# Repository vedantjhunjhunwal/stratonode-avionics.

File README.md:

# StratoNode: avionics power & telemetry node for stratospheric UAVs

A flight-computer-class board for a fixed-wing UAV cruising at **50,000 ft (15.5 km), -70 °C,
15% sea-level air density**: input protection and hold-up, a 5 V / 3 A buck and 3V3 LDO,
firmware-controlled load shedding, two heater channels (battery box and avionics bay), an
STM32G474 (Cortex-M4F, CAN-FD), a barometer good to 10 mbar, and GNSS (GPS + NavIC), telemetry,
payload and CAN harness connectors.

The project covers the board end to end: power budget and failure analysis, schematic,
component selection, PCB placement, embedded C firmware, and a closed-loop flight simulation
that runs that firmware against battery, thermal and power models.

## What has been verified, and what has not

| | Status |
|---|---|
| Power, thermal, hold-up, solder-fatigue and vibration analysis | Done: `analysis/`, 12 pytest tests, report in `docs/ANALYSIS.md` |
| Schematic (KiCad 7) | Done: 104 parts, 66 nets. KiCad's exported netlist matches the design source pin for pin (314 pins); an ERC subset passes (KiCad 7's CLI has no ERC). |
| PCB | **Placed, not yet routed.** 80 x 56 mm, 4 layers (GND and 3V3 inner planes), all footprints placed with no courtyard overlaps. Routing is one Freerouting run (see below). |
| Firmware | Drivers, power manager, heaters, NMEA, CAN-FD telemetry: 136 unit checks under AddressSanitizer/UBSan. Cross-compiles for the STM32G474 with no heap. **Not run on hardware**: I2C/SPI/UART/FDCAN peripheral drivers on the target are stubs until the board exists. |
| Flight simulation | 10.5 h mission, 5 seeds, firmware in the loop, with and without load shedding |
| Fabricated, built, flown | **No.** |

## Key results

**Power and thermal** (`docs/ANALYSIS.md`)
- Mission energy **135.8 Wh** (analysis) vs **136.5 Wh** (closed-loop simulation, mean of 5 seeds). Pack: **4S5P** 18650, 8% margin at end of life and +5 °C, with 20% reserve.
- Peak 5 V rail 1.91 A against the 3 A buck (36% margin). Junction temperatures checked at -70 °C cruise and +50 °C hot ground; all parts inside their ratings.
- Unheated, the avionics bay would settle at **-57.5 °C**, below the -40 °C rating of most parts. A 2 W bay heater holds -25 °C. The battery heater (12.6 W) warms a cold-soaked pack from -30 °C to +5 °C in 54 min.

**Design against failure**
- **Hold-up:** a 50 ms connector dropout under vibration needs **24,251 µF** if every load stays on, but only **999 µF** if firmware sheds the radio, payload *and both heaters* within 0.35 ms (INA226 ALERT → EXTI interrupt). Fitted: 3 × 470 µF polymer (1340 µF at -55 °C). The bulk caps are polymer, not electrolytic, because at -55 °C the electrolytics' ESR would add a 0.7 V step.
- **Simulation, 5 seeds, 153 dropouts of 2-50 ms:** **0 brownout resets** with load shedding vs **111** without.
- **Solder fatigue (Engelmaier, 1000-flight target at 0.1% failures):** 2512 shunts fail even in the heated bay, so the board uses 1206; the bay heater is what keeps 1206/1210 parts above target.
- **Vibration (Steinberg):** board fundamental 650 Hz, worst component deflection margin 6.2×.
- **Sensor faults:** a 20-minute battery-NTC open circuit is detected and ridden out on open-loop heater duty; 98 injected I2C bus lock-ups were all recovered by clocking out the stuck slave.
- **Data integrity:** all 3,795 injected CAN-FD bit errors caught (CRC-8 + alive counter). NMEA's XOR checksum let corrupted GNSS fixes through; a two-fix confirmation gate now holds the residual error to ≤100 m (11 of 36,403 corrupted sentences), where corrupted fixes previously got through with up to 15.5 km altitude error.

## Layout

```
analysis/   Python: ISA atmosphere, power budget, battery sizing, thermal, brown-out, hold-up,
            Engelmaier solder fatigue, Steinberg vibration. design.py holds every input.
hw/         parts.py (design source) -> gen_schematic.py -> KiCad schematic
            check_schematic.py (netlist round trip + ERC subset), gen_pcb.py (placement, planes,
            routing hand-off, DRC, Gerbers), make_bom.py
fw/         include/, src/   drivers (INA226, TMP117, MS5611, I2C recovery), power manager,
                             heater PI, NMEA (GPS+NavIC), CAN-FD telemetry, app layer
            tests/           unit tests with register-level fake devices
            sim/             closed-loop flight simulation
            target/          STM32G474 startup, linker script, register-level main, build script
results/    analysis.json, sim/*.json|csv, flight_sim.png, pcb_placement.png, schematic PDF
```

## Build and run

```bash
# analysis
(cd analysis && python3 -m pytest -q tests && python3 -m stratonode_analysis.report)
# firmware: unit tests, simulation campaign, STM32G474 cross-compile (gcc-arm-none-eabi, libnewlib-arm-none-eabi)
(cd fw && make test && make sim && make m4)
python3 tools/plot_sim.py
# hardware (KiCad 7 with its Python module)
cd hw && python3 gen_schematic.py && python3 check_schematic.py && python3 make_bom.py
python3 gen_pcb.py place && python3 gen_pcb.py route
java -jar freerouting-1.9.0.jar -de stratonode/stratonode.dsn -do stratonode/stratonode.ses -mp 40
python3 gen_pcb.py import      # routes in, outer GND pours, DRC report, Gerbers/drill/pos in stratonode/fab/
```

## Design notes

- **Why the ideal diode (LM74700 + N-FET):** reverse-polarity protection without a diode drop, and it
  stops the hold-up caps back-feeding a dropped input. VIN is sensed *before* it, so VIN collapses
  within microseconds of a connector opening while VBAT is still held up. That gap is how firmware
  sees a dropout in time to shed load.
- **Two I2C buses:** the external GNSS/compass harness is on I2C2, so a damaged cable cannot hang the
  INA226/TMP117 bus that the power and heater loops depend on.
- **Crystal, not RC:** CAN-FD bit timing needs better than 0.5% clock error at -40 °C.
- **Tag-Connect for SWD:** no debug header on board to vibrate loose in flight.
- **Pixhawk-standard JST-GH pinouts** for CAN, GNSS and telemetry, with positive latches.

## Limitations (read before quoting numbers)

- **Nothing here has been built or flown.** Thermal and electrical models use datasheet and typical
  values; anything marked ASSUMED in `analysis/stratonode_analysis/design.py` needs measuring.
- **The PCB is placed but not routed**, and DRC has not been run on a routed board. Before ordering:
  route, run DRC, and review the buck layout loop by hand. Check the TPS62933 RT/SS values and the
  MCU alternate-function pin map against the datasheets in STM32CubeMX.
- **Engelmaier and Steinberg are screening models.** Engelmaier is good to about a factor of 2; the
  vibration PSD is an assumed envelope, not a measured flight spectrum.
- **The simulation is not hardware-in-the-loop.** It checks that the logic is right, not its timing on the MCU.
- The thermal model treats each enclosure as a single lumped node, and cold-day ISA as the ambient.

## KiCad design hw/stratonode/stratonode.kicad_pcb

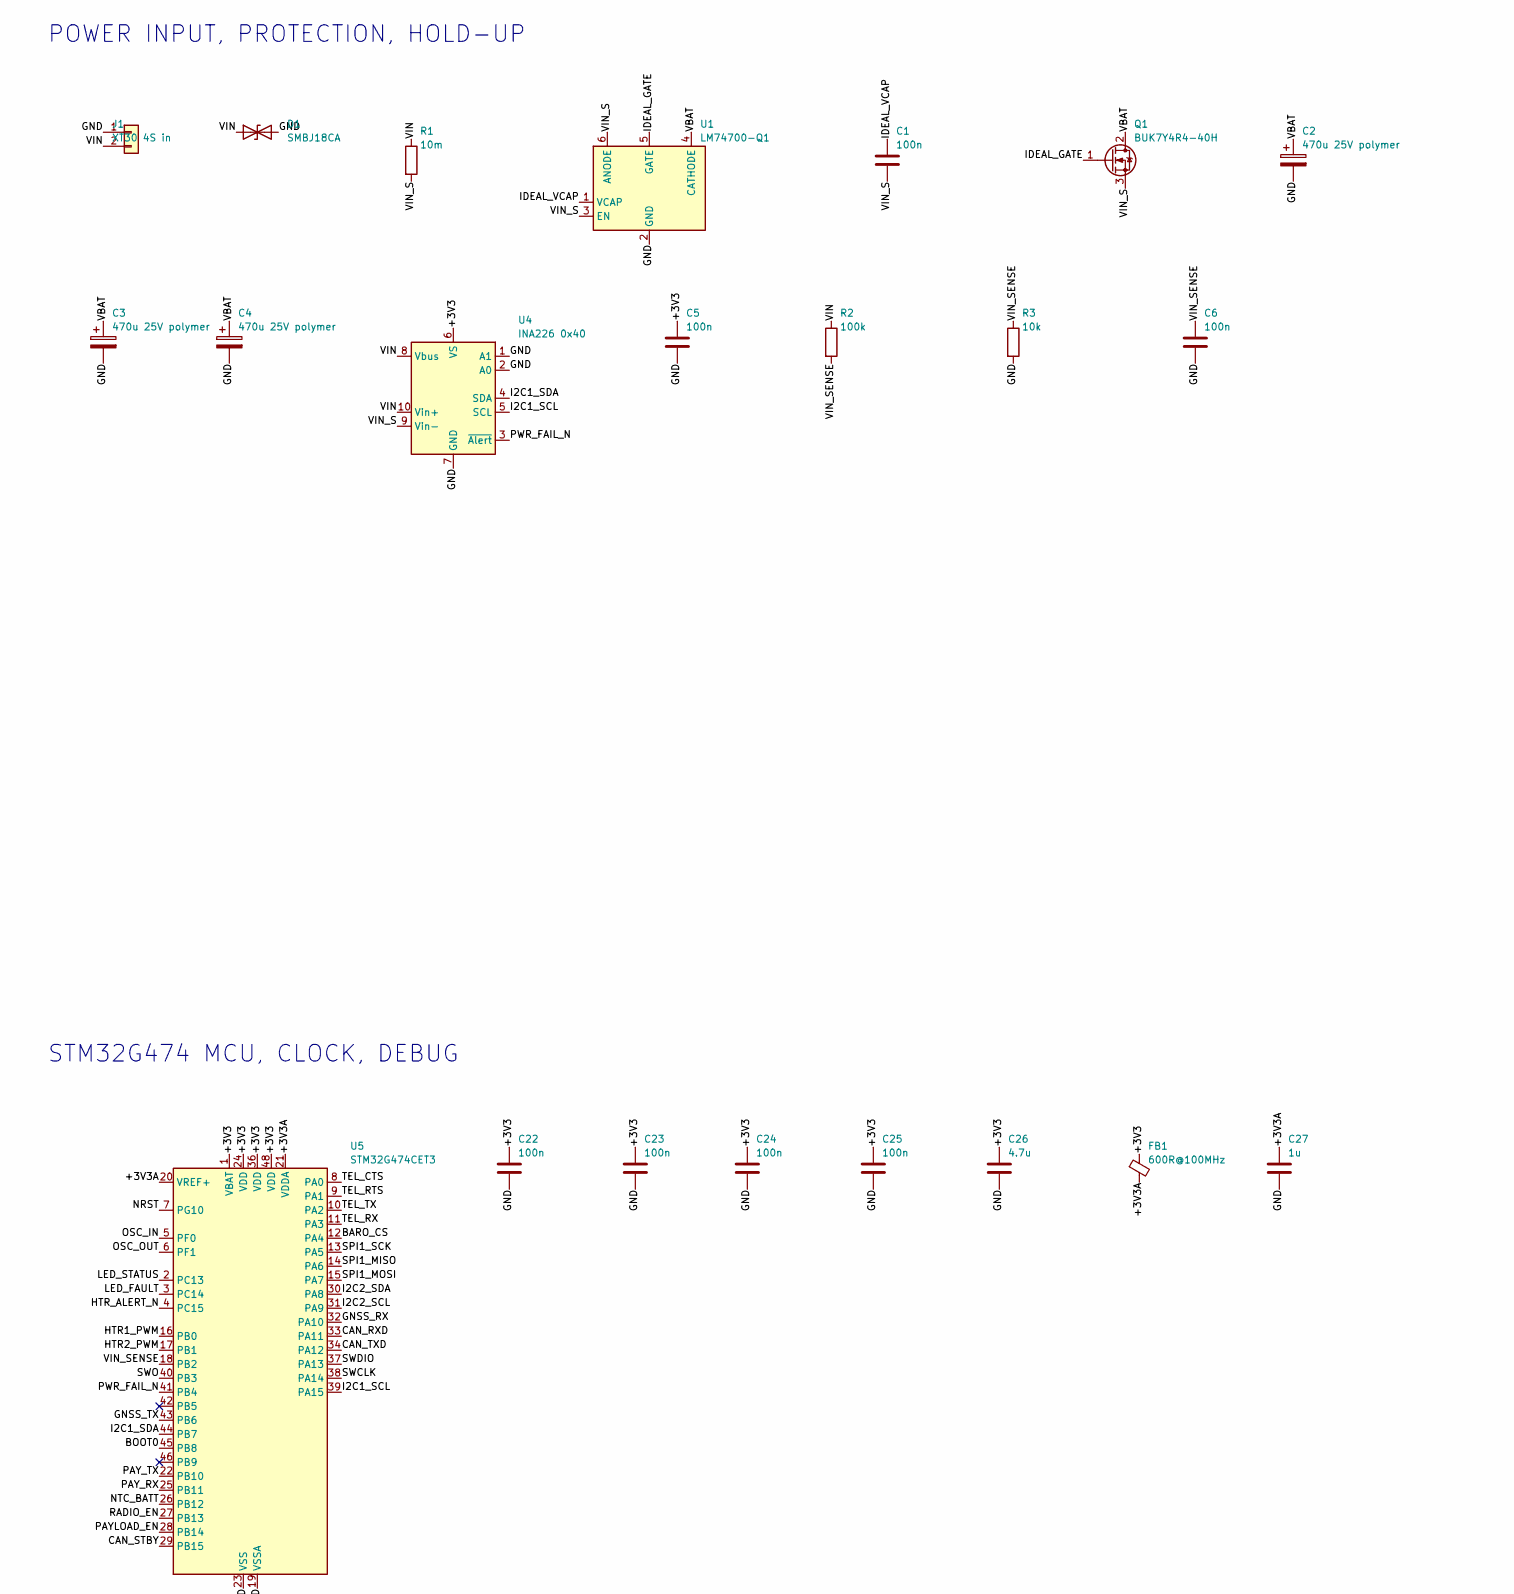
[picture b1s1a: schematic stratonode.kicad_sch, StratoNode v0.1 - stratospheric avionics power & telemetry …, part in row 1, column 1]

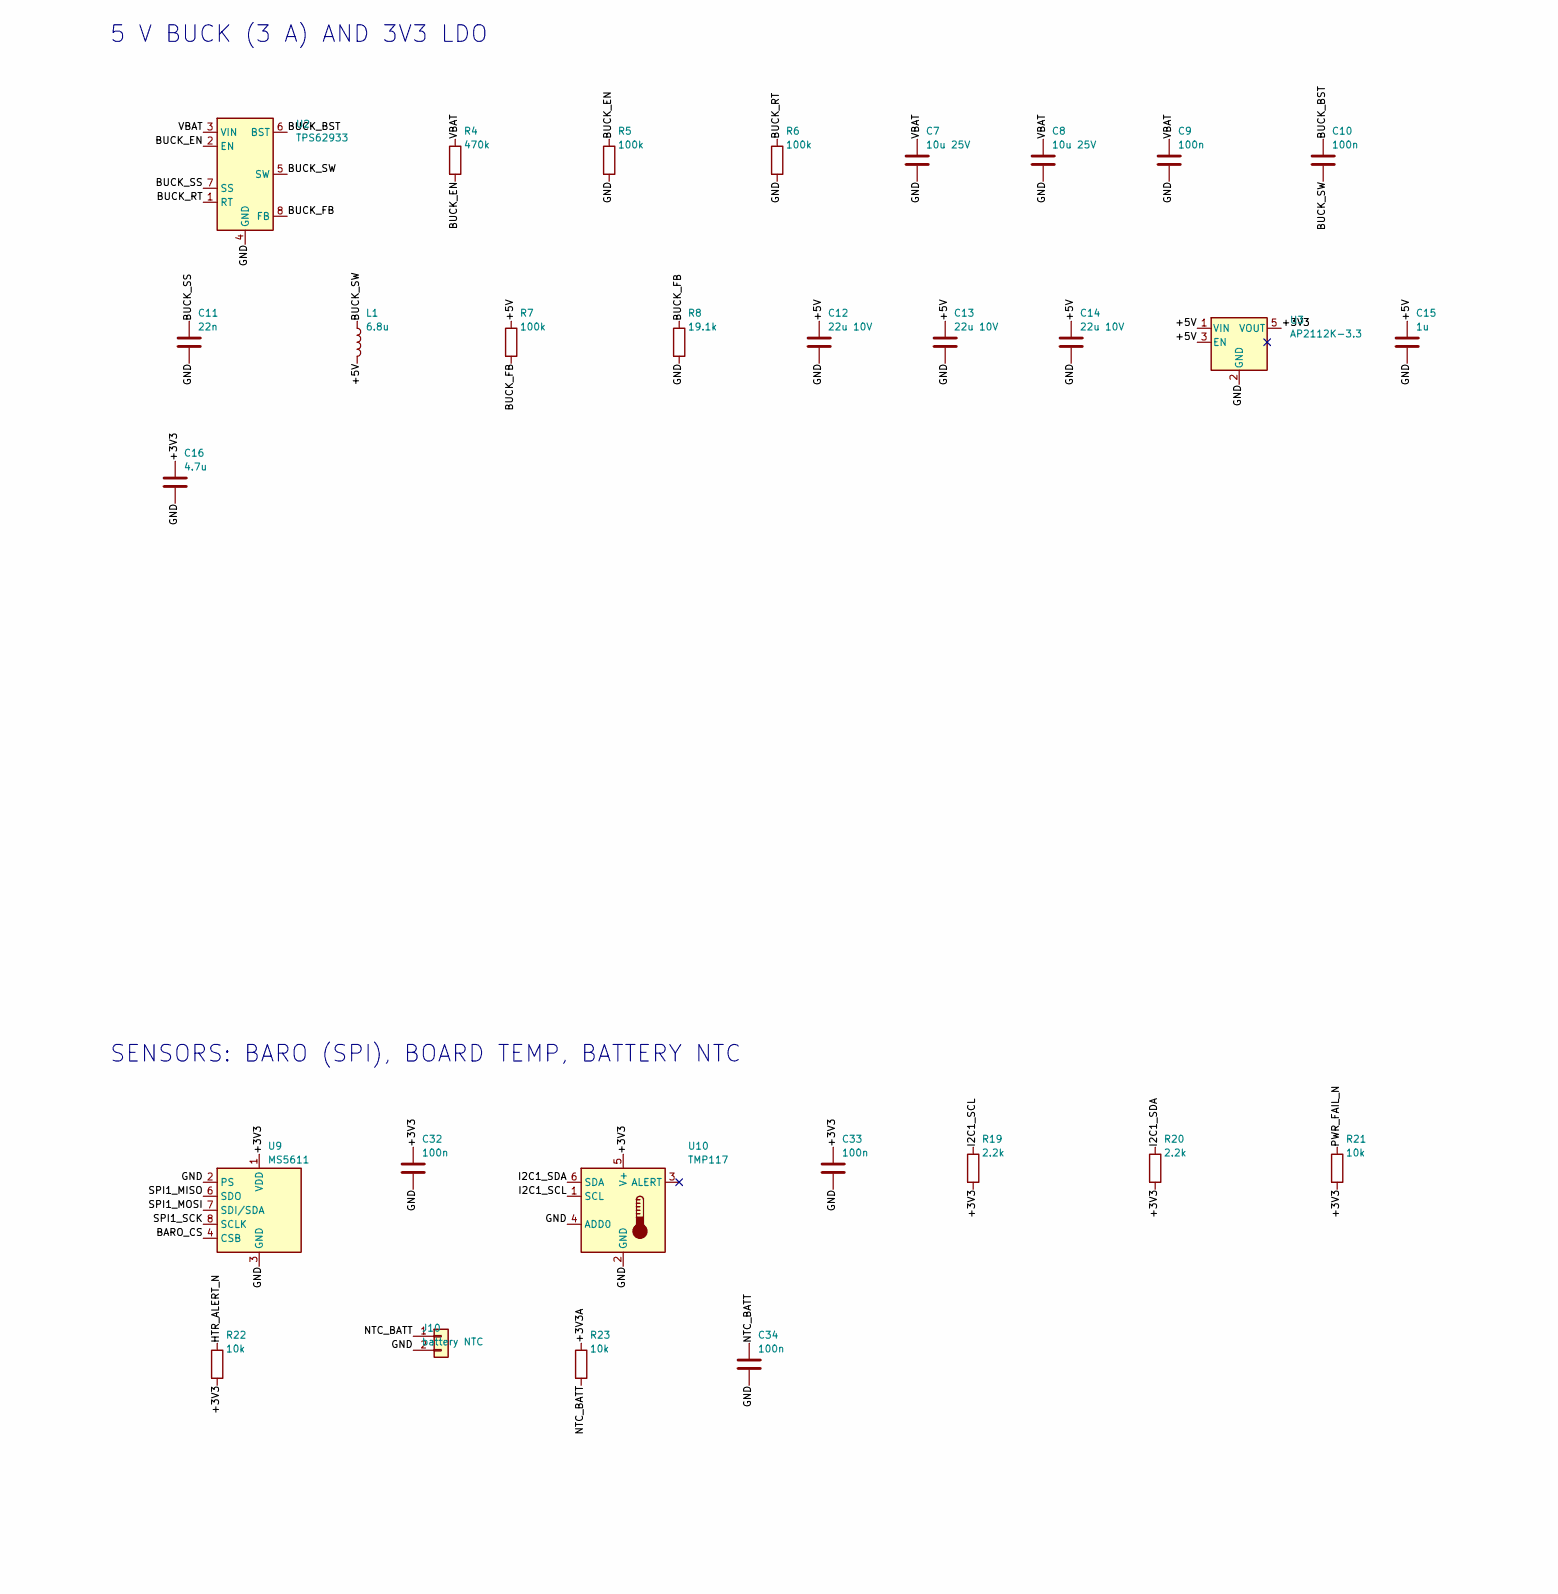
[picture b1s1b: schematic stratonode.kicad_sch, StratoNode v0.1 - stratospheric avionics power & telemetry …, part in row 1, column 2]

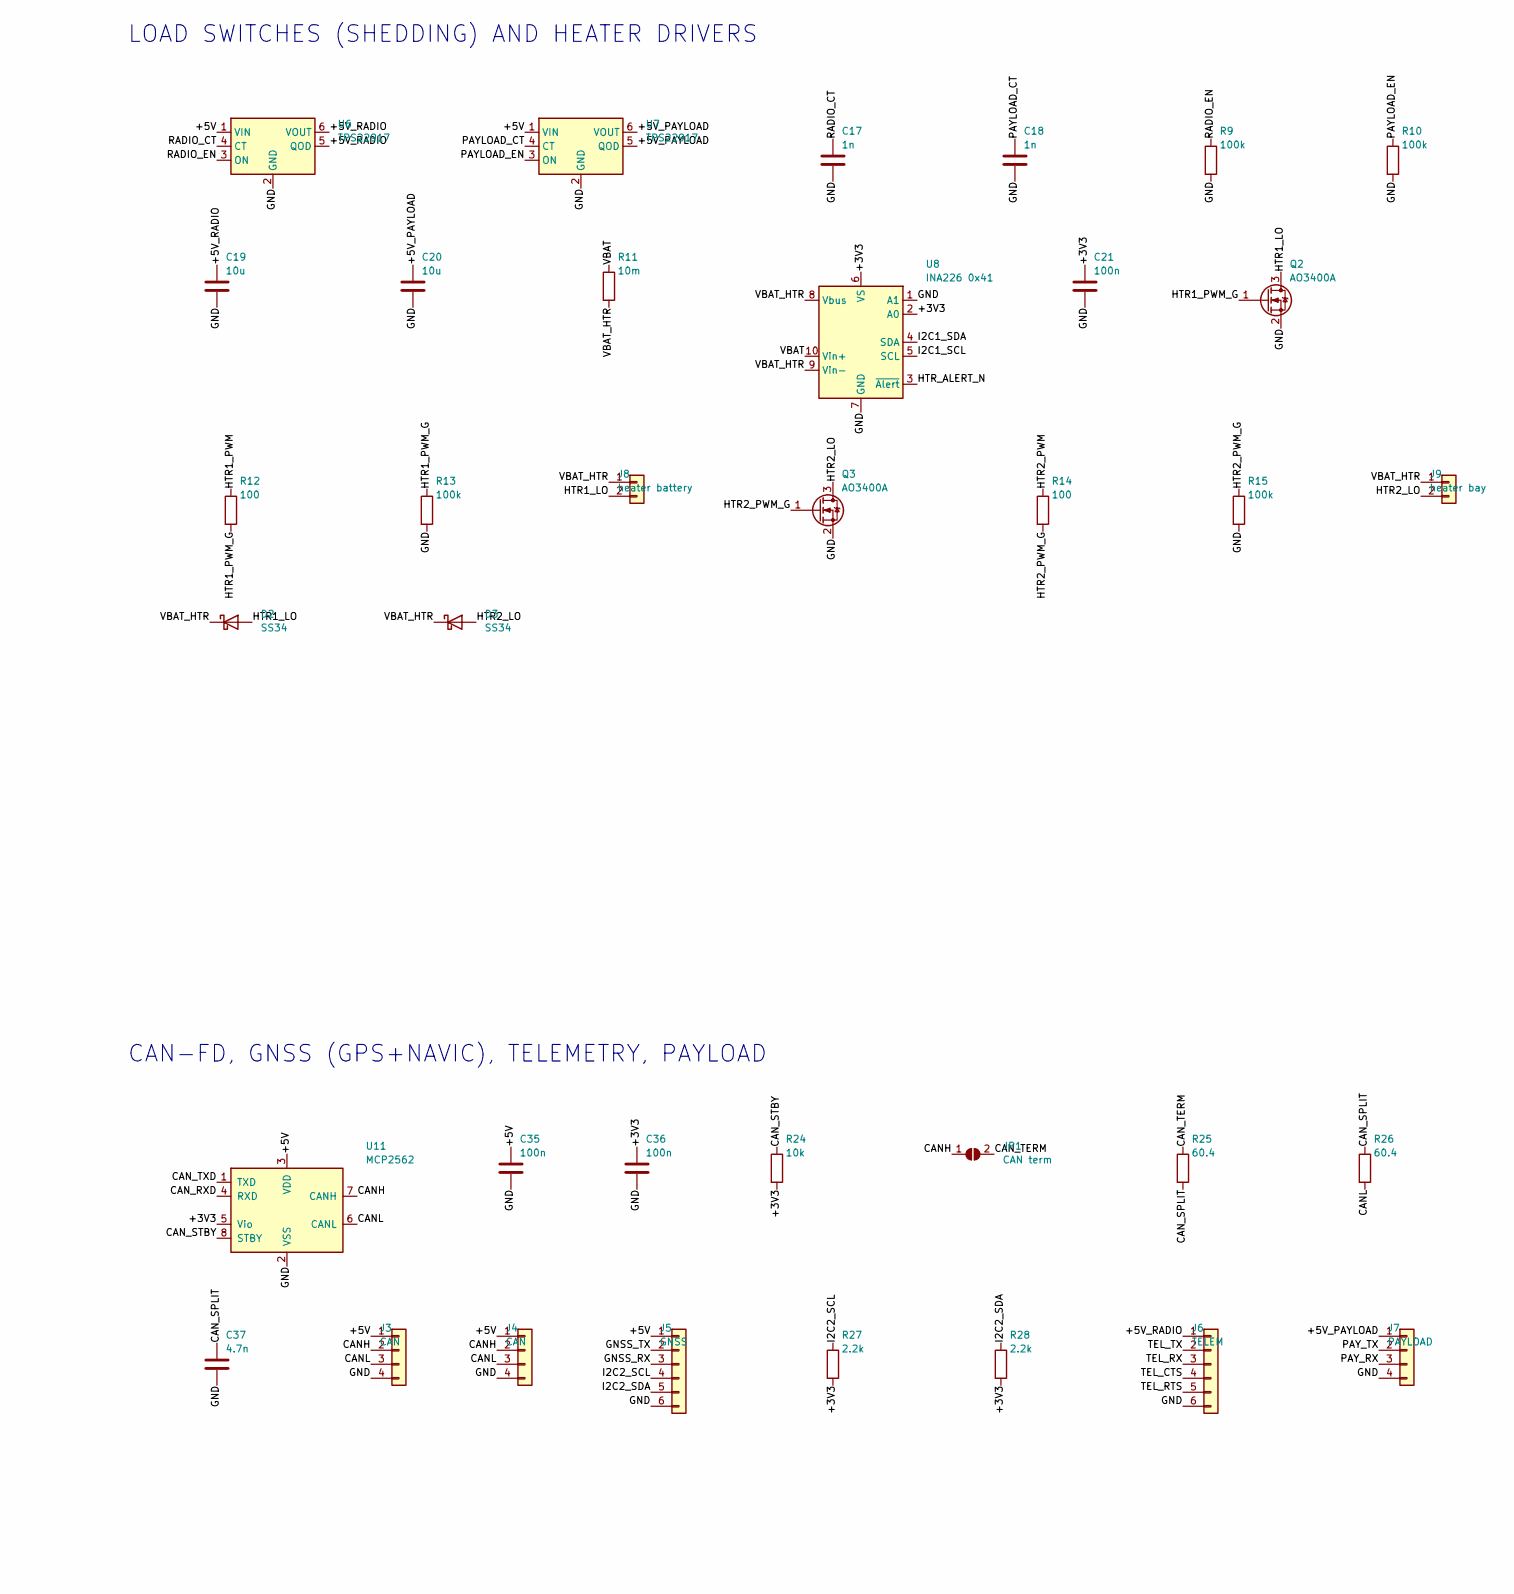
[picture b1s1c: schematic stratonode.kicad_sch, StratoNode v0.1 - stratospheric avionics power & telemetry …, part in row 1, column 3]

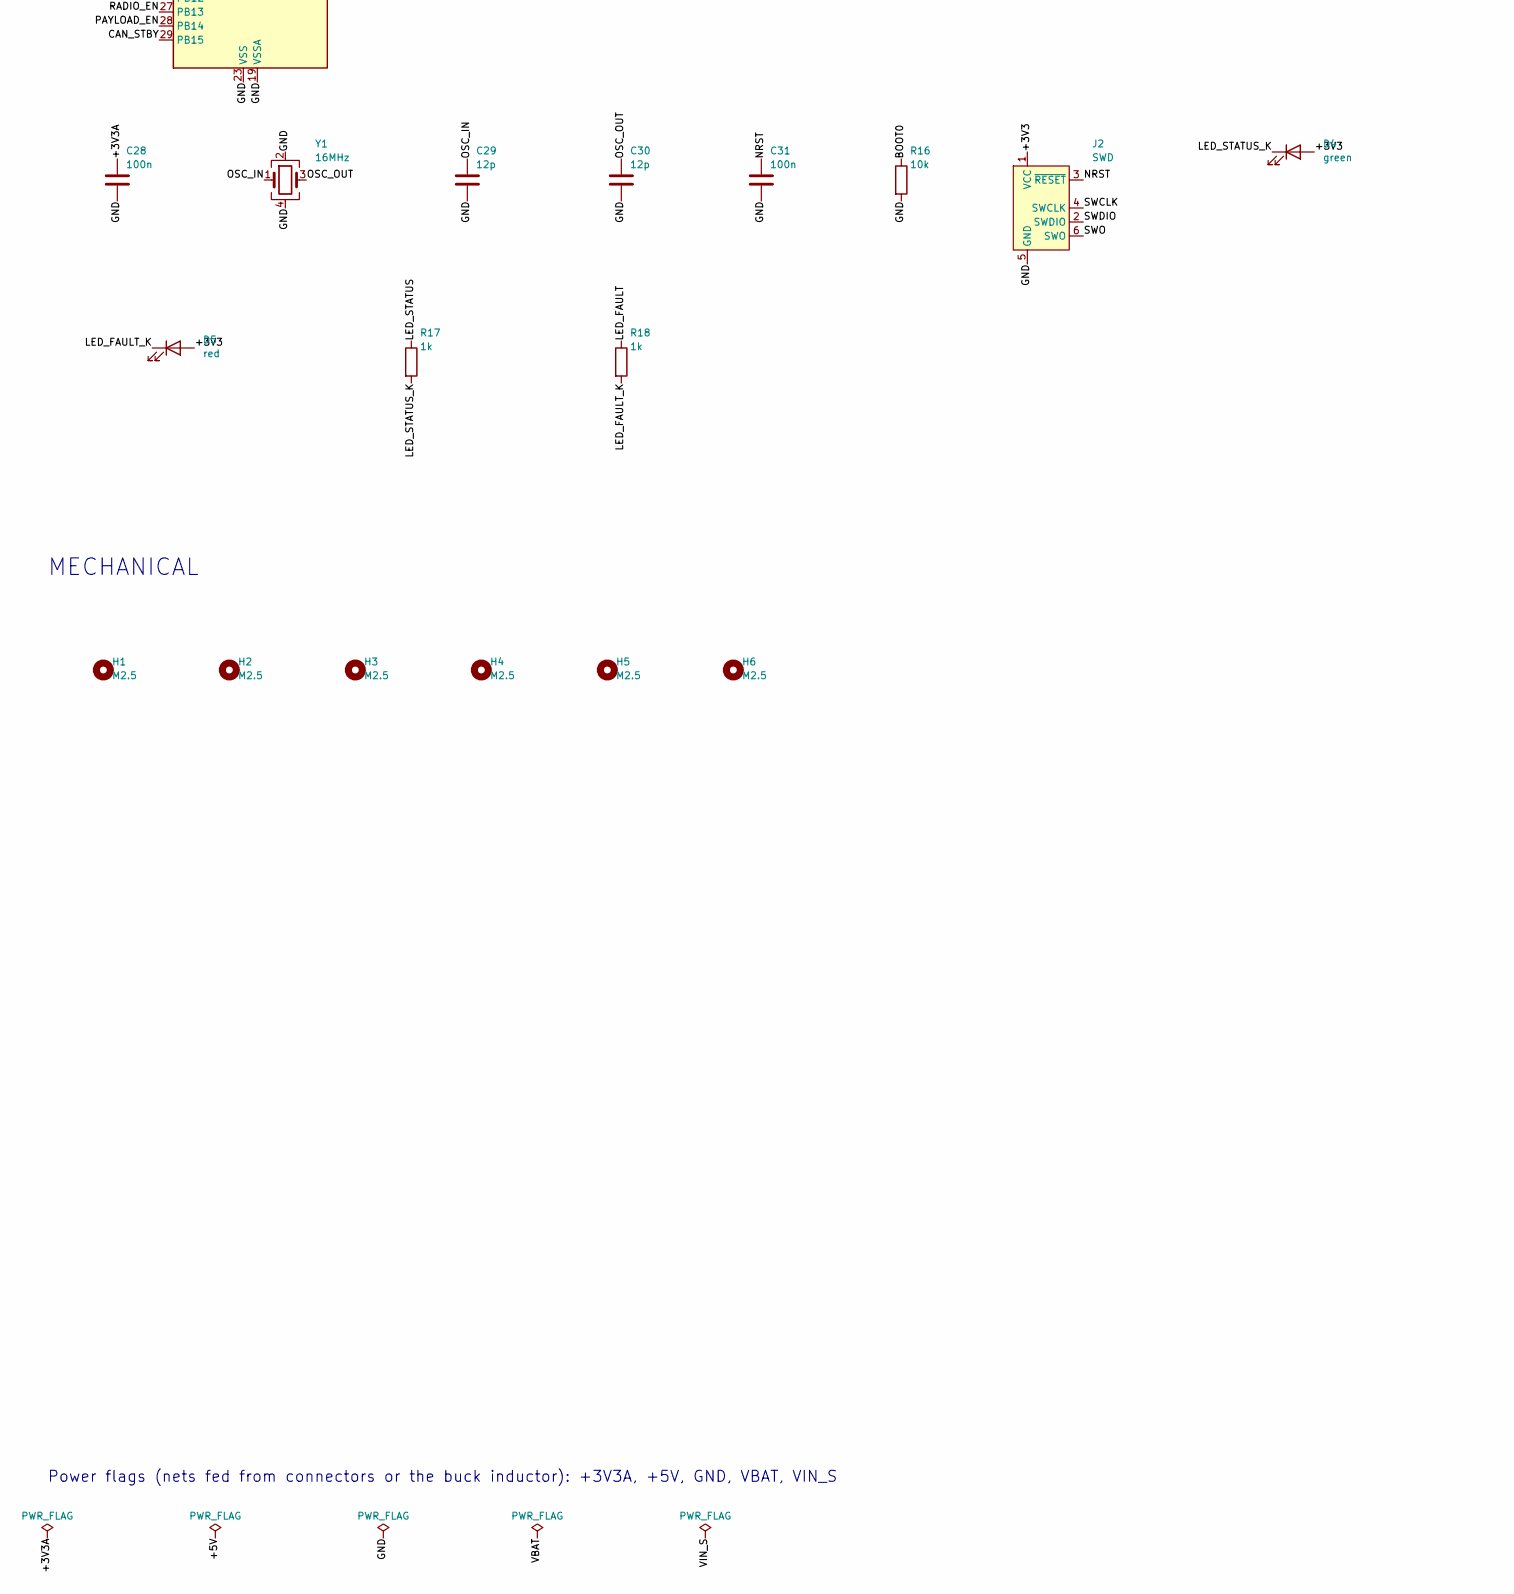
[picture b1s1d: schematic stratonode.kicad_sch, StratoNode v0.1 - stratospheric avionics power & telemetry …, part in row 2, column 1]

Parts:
C1, C5, C6, C9, C10, C21, C22, C23, C24, C25, C28, C31, C32, C33, C34, C35, C36: 100n; C_0603_1608Metric; MPN 100n X7R, -55..125 C
C2, C3, C4: 470u 25V polymer; CP_Elec_8x10; MPN 25 V 470 uF aluminium polymer, -55..105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
C7, C8: 10u 25V; C_0805_2012Metric; MPN 10u 25V X7R, -55..125 C
C11: 22n; C_0603_1608Metric; MPN 22n X7R, -55..125 C
C12, C13, C14: 22u 10V; C_0805_2012Metric; MPN 22u 10V X7R, -55..125 C
C15, C27: 1u; C_0603_1608Metric; MPN 1u X7R, -55..125 C
C16, C26: 4.7u; C_0805_2012Metric; MPN 4.7u X7R, -55..125 C
C17, C18: 1n; C_0603_1608Metric; MPN 1n X7R, -55..125 C
C19, C20: 10u; C_0805_2012Metric; MPN 10u X7R, -55..125 C
C29, C30: 12p; C_0603_1608Metric; MPN 12 pF C0G
C37: 4.7n; C_0603_1608Metric; MPN 4.7n X7R, -55..125 C
D1: SMBJ18CA; D_SMB; MPN SMBJ18CA
D2, D3: SS34; D_SMA; MPN SS34
D4: green; LED_0603_1608Metric; MPN green 0603 LED
D5: red; LED_0603_1608Metric; MPN red 0603 LED
FB1: 600R@100MHz; L_0603_1608Metric; MPN BLM18KG601SN1D
H1, H2, H3, H4, H5, H6: M2.5; MountingHole_2.7mm_M2.5; MPN M2.5 standoff
J1: XT30 4S in; AMASS_XT30PW-M_1x02_P2.50mm_Horizontal; MPN AMASS XT30PW-M
J2: SWD; Tag-Connect_TC2030-IDC-NL_2x03_P1.27mm_Vertical; MPN Tag-Connect TC2030-NL
J3, J4: CAN; JST_GH_SM04B-GHS-TB_1x04-1MP_P1.25mm_Horizontal; MPN JST SM04B-GHS-TB
J5: GNSS; JST_GH_SM06B-GHS-TB_1x06-1MP_P1.25mm_Horizontal; MPN JST SM06B-GHS-TB
J6: TELEM; JST_GH_SM06B-GHS-TB_1x06-1MP_P1.25mm_Horizontal; MPN JST SM06B-GHS-TB
J7: PAYLOAD; JST_GH_SM04B-GHS-TB_1x04-1MP_P1.25mm_Horizontal; MPN JST SM04B-GHS-TB
J8: heater battery; JST_XH_B2B-XH-A_1x02_P2.50mm_Vertical; MPN JST B2B-XH-A
J9: heater bay; JST_XH_B2B-XH-A_1x02_P2.50mm_Vertical; MPN JST B2B-XH-A
J10: battery NTC; JST_GH_SM02B-GHS-TB_1x02-1MP_P1.25mm_Horizontal; MPN JST SM02B-GHS-TB
JP1: CAN term; SolderJumper-2_P1.3mm_Open_RoundedPad1.0x1.5mm
L1: 6.8u; L_Bourns_SRP7028A_7.3x6.6mm; MPN Bourns SRP7028A-6R8M
Q1: BUK7Y4R4-40H; TO-252-2; MPN 40 V, 4.4 mOhm N-FET (ideal diode)
Q2, Q3: AO3400A; SOT-23; MPN AO3400A
R1, R11: 10m; R_1206_3216Metric; MPN 10 mOhm 1206 0.5 W current shunt
R2, R5, R6, R7, R9, R10, R13, R15: 100k; R_0603_1608Metric; MPN 100k 1% 0603, AEC-Q200, -55..155 C
R3, R16, R21, R22, R23, R24: 10k; R_0603_1608Metric; MPN 10k 1% 0603, AEC-Q200, -55..155 C
R4: 470k; R_0603_1608Metric; MPN 470k 1% 0603, AEC-Q200, -55..155 C
R8: 19.1k; R_0603_1608Metric; MPN 19.1k 1% 0603, AEC-Q200, -55..155 C
R12, R14: 100; R_0603_1608Metric; MPN 100 1% 0603, AEC-Q200, -55..155 C
R17, R18: 1k; R_0603_1608Metric; MPN 1k 1% 0603, AEC-Q200, -55..155 C
R19, R20, R27, R28: 2.2k; R_0603_1608Metric; MPN 2.2k 1% 0603, AEC-Q200, -55..155 C
R25, R26: 60.4; R_0603_1608Metric; MPN 60.4 1% 0603, AEC-Q200, -55..155 C
U1: LM74700-Q1; SOT-23-6; MPN LM74700QDBVRQ1
U2: TPS62933; SOT-583-8; MPN TPS62933DRLR
U3: AP2112K-3.3; SOT-23-5; MPN AP2112K-3.3TRG1
U4: INA226 0x40; VSSOP-10_3x3mm_P0.5mm; MPN INA226AIDGSR
U5: STM32G474CET3; LQFP-48_7x7mm_P0.5mm; MPN STM32G474CET3
U6, U7: TPS22917; SOT-23-6; MPN TPS22917DBVR
U8: INA226 0x41; VSSOP-10_3x3mm_P0.5mm; MPN INA226AIDGSR
U9: MS5611; LGA-8_3x5mm_P1.25mm; MPN MS561101BA03-50
U10: TMP117; WSON-6-1EP_2x2mm_P0.65mm_EP1x1.6mm; MPN TMP117MAIDRVR
U11: MCP2562; SOIC-8_3.9x4.9mm_P1.27mm; MPN MCP2562FD-E/SN
Y1: 16MHz; Crystal_SMD_3225-4Pin_3.2x2.5mm; MPN 16 MHz 10 pF, -40..125 C

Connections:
+3V3: C5.1, C16.1, C21.1, C22.1, C23.1, C24.1, C25.1, C26.1, C32.1, C33.1, C36.1, D4.2 (A), D5.2 (A), FB1.1, J2.1 (VCC), R19.2, R20.2, R21.2, R22.2, R24.2, R27.2, R28.2, U3.5 (VOUT), U4.6 (VS), U5.1 (VBAT), U5.24 (VDD), U5.36 (VDD), U5.48 (VDD), U8.2 (A0), U8.6 (VS), U9.1 (VDD), U10.5 (V+), U11.5 (Vio)
+3V3A: C27.1, C28.1, FB1.2, R23.1, U5.20 (VREF+), U5.21 (VDDA)
+5V: C12.1, C13.1, C14.1, C15.1, C35.1, J3.1, J4.1, J5.1, L1.2, R7.1, U3.1 (VIN), U3.3 (EN), U6.1 (VIN), U7.1 (VIN), U11.3 (VDD)
+5V_PAYLOAD: C20.1, J7.1, U7.5 (QOD), U7.6 (VOUT)
+5V_RADIO: C19.1, J6.1, U6.5 (QOD), U6.6 (VOUT)
BARO_CS: U5.12 (PA4), U9.4 (CSB), U9.5 (CSB)
BOOT0: R16.1, U5.45 (PB8)
BUCK_BST: C10.1, U2.6 (BST)
BUCK_EN: R4.2, R5.1, U2.2 (EN)
BUCK_FB: R7.2, R8.1, U2.8 (FB)
BUCK_RT: R6.1, U2.1 (RT)
BUCK_SS: C11.1, U2.7 (SS)
BUCK_SW: C10.2, L1.1, U2.5 (SW)
CANH: J3.2, J4.2, JP1.1 (A), U11.7 (CANH)
CANL: J3.3, J4.3, R26.2, U11.6 (CANL)
CAN_RXD: U5.33 (PA11), U11.4 (RXD)
CAN_SPLIT: C37.1, R25.2, R26.1
CAN_STBY: R24.1, U5.29 (PB15), U11.8 (STBY)
CAN_TERM: JP1.2 (B), R25.1
CAN_TXD: U5.34 (PA12), U11.1 (TXD)
GND: C2.2, C3.2, C4.2, C5.2, C6.2, C7.2, C8.2, C9.2, C11.2, C12.2, C13.2, C14.2, C15.2, C16.2, C17.2, C18.2, C19.2, C20.2, C21.2, C22.2, C23.2, C24.2, C25.2, C26.2, C27.2, C28.2, C29.2, C30.2, C31.2, C32.2, C33.2, C34.2, C35.2, C36.2, C37.2, D1.2 (A2), J1.1, J2.5 (GND), J3.4, J4.4, J5.6, J6.6, J7.4, J10.2, Q2.2 (S), Q3.2 (S), R3.2, R5.2, R6.2, R8.2, R9.2, R10.2, R13.2, R15.2, R16.2, U1.2 (GND), U2.4 (GND), U3.2 (GND), U4.1 (A1), U4.2 (A0), U4.7 (GND), U5.19 (VSSA), U5.23 (VSS), U5.35 (VSS), U5.47 (VSS), U6.2 (GND), U7.2 (GND), U8.1 (A1), U8.7 (GND), U9.2 (PS), U9.3 (GND), U10.2 (GND), U10.4 (ADD0), U11.2 (VSS), Y1.2, Y1.4
GNSS_RX: J5.3, U5.32 (PA10)
GNSS_TX: J5.2, U5.43 (PB6)
HTR1_LO: D2.2 (A), J8.2, Q2.3 (D)
HTR1_PWM: R12.1, U5.16 (PB0)
HTR1_PWM_G: Q2.1 (G), R12.2, R13.1
HTR2_LO: D3.2 (A), J9.2, Q3.3 (D)
HTR2_PWM: R14.1, U5.17 (PB1)
HTR2_PWM_G: Q3.1 (G), R14.2, R15.1
HTR_ALERT_N: R22.1, U5.4 (PC15), U8.3 (~Alert)
I2C1_SCL: R19.1, U4.5 (SCL), U5.39 (PA15), U8.5 (SCL), U10.1 (SCL)
I2C1_SDA: R20.1, U4.4 (SDA), U5.44 (PB7), U8.4 (SDA), U10.6 (SDA)
I2C2_SCL: J5.4, R27.1, U5.31 (PA9)
I2C2_SDA: J5.5, R28.1, U5.30 (PA8)
IDEAL_GATE: Q1.1 (G), U1.5 (GATE)
IDEAL_VCAP: C1.1, U1.1 (VCAP)
LED_FAULT: R18.1, U5.3 (PC14)
LED_FAULT_K: D5.1 (K), R18.2
LED_STATUS: R17.1, U5.2 (PC13)
LED_STATUS_K: D4.1 (K), R17.2
NRST: C31.1, J2.3 (~RESET), U5.7 (PG10)
NTC_BATT: C34.1, J10.1, R23.2, U5.26 (PB12)
OSC_IN: C29.1, U5.5 (PF0), Y1.1
OSC_OUT: C30.1, U5.6 (PF1), Y1.3
PAYLOAD_CT: C18.1, U7.4 (CT)
PAYLOAD_EN: R10.1, U5.28 (PB14), U7.3 (ON)
PAY_RX: J7.3, U5.25 (PB11)
PAY_TX: J7.2, U5.22 (PB10)
PWR_FAIL_N: R21.1, U4.3 (~Alert), U5.41 (PB4)
RADIO_CT: C17.1, U6.4 (CT)
RADIO_EN: R9.1, U5.27 (PB13), U6.3 (ON)
SPI1_MISO: U5.14 (PA6), U9.6 (SDO)
SPI1_MOSI: U5.15 (PA7), U9.7 (SDI/SDA)
SPI1_SCK: U5.13 (PA5), U9.8 (SCLK)
SWCLK: J2.4 (SWCLK), U5.38 (PA14)
SWDIO: J2.2 (SWDIO), U5.37 (PA13)
SWO: J2.6 (SWO), U5.40 (PB3)
TEL_CTS: J6.4, U5.8 (PA0)
TEL_RTS: J6.5, U5.9 (PA1)
TEL_RX: J6.3, U5.11 (PA3)
TEL_TX: J6.2, U5.10 (PA2)
VBAT: C2.1, C3.1, C4.1, C7.1, C8.1, C9.1, Q1.2 (D), R4.1, R11.1, U1.4 (CATHODE), U2.3 (VIN), U8.10 (Vin+)
VBAT_HTR: D2.1 (K), D3.1 (K), J8.1, J9.1, R11.2, U8.8 (Vbus), U8.9 (Vin-)
VIN: D1.1 (A1), J1.2, R1.1, R2.1, U4.8 (Vbus), U4.10 (Vin+)
VIN_S: C1.2, Q1.3 (S), R1.2, U1.3 (EN), U1.6 (ANODE), U4.9 (Vin-)
VIN_SENSE: C6.1, R2.2, R3.1, U5.18 (PB2)

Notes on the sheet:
POWER INPUT, PROTECTION, HOLD-UP
5 V BUCK (3 A) AND 3V3 LDO
LOAD SWITCHES (SHEDDING) AND HEATER DRIVERS
STM32G474 MCU, CLOCK, DEBUG
SENSORS: BARO (SPI), BOARD TEMP, BATTERY NTC
CAN-FD, GNSS (GPS+NAVIC), TELEMETRY, PAYLOAD
MECHANICAL
Power flags (nets fed from connectors or the buck inductor): +3V3A, +5V, GND, VBAT, VIN_S

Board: 4 copper layers, 104 parts (0 on the bottom side), 66 nets, no tracks yet.

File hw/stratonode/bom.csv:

Qty,References,Value,Part / rating,Footprint,Why this part
17,C1 C5 C6 C9 C10 C21 C22 C23 C24 C25 C28 C31 C32 C33 C34 C35 C36,100n,"100n X7R, -55..125 C",C_0603_1608Metric,ADC analog-watchdog input: fast dropout detection
1,C11,22n,"22n X7R, -55..125 C",C_0603_1608Metric,
3,C12 C13 C14,22u 10V,"22u 10V X7R, -55..125 C",C_0805_2012Metric,
2,C15 C27,1u,"1u X7R, -55..125 C",C_0603_1608Metric,
2,C16 C26,4.7u,"4.7u X7R, -55..125 C",C_0805_2012Metric,
2,C17 C18,1n,"1n X7R, -55..125 C",C_0603_1608Metric,slew rate: limits inrush from radio input caps
2,C19 C20,10u,"10u X7R, -55..125 C",C_0805_2012Metric,
3,C2 C3 C4,470u 25V polymer,"25 V 470 uF aluminium polymer, -55..105 C",CP_Elec_8x10,hold-up: 3 x 470 uF rides a 50 ms dropout with load shedding
2,C29 C30,12p,12 pF C0G,C_0603_1608Metric,
1,C37,4.7n,"4.7n X7R, -55..125 C",C_0603_1608Metric,
2,C7 C8,10u 25V,"10u 25V X7R, -55..125 C",C_0805_2012Metric,
1,D1,SMBJ18CA,SMBJ18CA,D_SMB,bidirectional TVS: clamps load dump below the buck's 30 V rating; blocks nothing
2,D2 D3,SS34,SS34,D_SMA,clamps harness-inductance kickback at heater switch-off
1,D4,green,green 0603 LED,LED_0603_1608Metric,
1,D5,red,red 0603 LED,LED_0603_1608Metric,
1,FB1,600R@100MHz,BLM18KG601SN1D,L_0603_1608Metric,isolates the ADC reference from digital noise
6,H1 H2 H3 H4 H5 H6,M2.5,M2.5 standoff,MountingHole_2.7mm_M2.5,
1,J1,XT30 4S in,AMASS XT30PW-M,AMASS_XT30PW-M_1x02_P2.50mm_Horizontal,locking-friction power connector; 4S pack 12.0-16.8 V
1,J10,battery NTC,JST SM02B-GHS-TB,JST_GH_SM02B-GHS-TB_1x02-1MP_P1.25mm_Horizontal,10k NTC on the cells
1,J2,SWD,Tag-Connect TC2030-NL,Tag-Connect_TC2030-IDC-NL_2x03_P1.27mm_Vertical,no connector fitted: nothing to vibrate loose in flight
2,J3 J4,CAN,JST SM04B-GHS-TB,JST_GH_SM04B-GHS-TB_1x04-1MP_P1.25mm_Horizontal,"Pixhawk-standard CAN pinout, daisy-chain in/out; GH has a positive latch"
1,J5,GNSS,JST SM06B-GHS-TB,JST_GH_SM06B-GHS-TB_1x06-1MP_P1.25mm_Horizontal,external GNSS (GPS+NavIC) + compass; its I2C is a separate bus so a harness fault can't hang internal sensors
1,J6,TELEM,JST SM06B-GHS-TB,JST_GH_SM06B-GHS-TB_1x06-1MP_P1.25mm_Horizontal,"telemetry radio, hardware flow control"
1,J7,PAYLOAD,JST SM04B-GHS-TB,JST_GH_SM04B-GHS-TB_1x04-1MP_P1.25mm_Horizontal,
1,J8,heater battery,JST B2B-XH-A,JST_XH_B2B-XH-A_1x02_P2.50mm_Vertical,3 A contacts; heater element 16 ohm (battery) / 47 ohm (bay)
1,J9,heater bay,JST B2B-XH-A,JST_XH_B2B-XH-A_1x02_P2.50mm_Vertical,3 A contacts; heater element 16 ohm (battery) / 47 ohm (bay)
1,JP1,CAN term,,SolderJumper-2_P1.3mm_Open_RoundedPad1.0x1.5mm,close on the node at the end of the bus
1,L1,6.8u,Bourns SRP7028A-6R8M,L_Bourns_SRP7028A_7.3x6.6mm,"6.8 uH, Isat > 5 A"
1,Q1,BUK7Y4R4-40H,"40 V, 4.4 mOhm N-FET (ideal diode)",TO-252-2,
2,Q2 Q3,AO3400A,AO3400A,SOT-23,"30 V 5.7 A logic-level N-FET, low-side heater switch"
2,R1 R11,10m,10 mOhm 1206 0.5 W current shunt,R_1206_3216Metric,1206 not 2512: solder-fatigue analysis
2,R12 R14,100,"100 1% 0603, AEC-Q200, -55..155 C",R_0603_1608Metric,
2,R17 R18,1k,"1k 1% 0603, AEC-Q200, -55..155 C",R_0603_1608Metric,
4,R19 R20 R27 R28,2.2k,"2.2k 1% 0603, AEC-Q200, -55..155 C",R_0603_1608Metric,I2C1 internal bus pull-ups
8,R2 R5 R6 R7 R9 R10 R13 R15,100k,"100k 1% 0603, AEC-Q200, -55..155 C",R_0603_1608Metric,sets switching frequency; check value against datasheet RT table
2,R25 R26,60.4,"60.4 1% 0603, AEC-Q200, -55..155 C",R_0603_1608Metric,split termination 2 x 60.4 ohm + 4.7 nF: EMI common-mode filter
6,R3 R16 R21 R22 R23 R24,10k,"10k 1% 0603, AEC-Q200, -55..155 C",R_0603_1608Metric,"NTC divider, 0.1%"
1,R4,470k,"470k 1% 0603, AEC-Q200, -55..155 C",R_0603_1608Metric,EN divider: turns on above ~6.9 V
1,R8,19.1k,"19.1k 1% 0603, AEC-Q200, -55..155 C",R_0603_1608Metric,
1,U1,LM74700-Q1,LM74700QDBVRQ1,SOT-23-6,"ideal-diode controller: reverse-polarity block, and stops the hold-up caps back-feeding a dropped input"
1,U10,TMP117,TMP117MAIDRVR,WSON-6-1EP_2x2mm_P0.65mm_EP1x1.6mm,"+/-0.1 C board temperature, 0x48; feeds the bay heater loop"
1,U11,MCP2562,MCP2562FD-E/SN,SOIC-8_3.9x4.9mm_P1.27mm,"CAN-FD transceiver, 5 V bus side, 3.3 V logic (Vio)"
1,U2,TPS62933,TPS62933DRLR,SOT-583-8,"3.8-30 V in, 3 A synchronous buck, -40..150 C junction"
1,U3,AP2112K-3.3,AP2112K-3.3TRG1,SOT-23-5,"600 mA LDO, -40..85 C ambient"
1,U4,INA226 0x40,INA226AIDGSR,VSSOP-10_3x3mm_P0.5mm,input V/I monitor; ALERT = bus under-voltage -> load shedding
1,U5,STM32G474CET3,STM32G474CET3,LQFP-48_7x7mm_P0.5mm,"170 MHz Cortex-M4F, FDCAN, -40..125 C grade"
2,U6 U7,TPS22917,TPS22917DBVR,SOT-23-6,"2 A load switch, ~1 us turn-off: firmware sheds this rail on power-fail"
1,U8,INA226 0x41,INA226AIDGSR,VSSOP-10_3x3mm_P0.5mm,heater current: detects open/shorted heater element
1,U9,MS5611,MS561101BA03-50,LGA-8_3x5mm_P1.25mm,"10-1200 mbar: covers 50,000 ft (~116 mbar); PS low = SPI"
1,Y1,16MHz,"16 MHz 10 pF, -40..125 C",Crystal_SMD_3225-4Pin_3.2x2.5mm,"crystal, not RC: FDCAN bit timing needs <0.5% clock error at -40 C"

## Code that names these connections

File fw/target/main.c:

/* STM32G474CE target: register-level bring-up of the parts the flight logic needs first.
 *
 * Done here: SysTick 1 ms tick, load-switch GPIOs (PB13 radio, PB14 payload), TIM3 CH3/CH4 heater
 * PWM on PB0/PB1 (1 kHz), INA226 ALERT on PB4 -> EXTI4 power-fail interrupt, independent watchdog.
 * Not yet done (needs the board): the I2C1/I2C2, SPI1, USART1-3 and FDCAN1 peripheral drivers
 * behind hal_i2c_t / hal_spi_t; the stubs below return HAL_TIMEOUT so the app runs in its
 * sensor-fault fallback. Clock stays on the 16 MHz HSI until the HSE/PLL bring-up.
 */
#include <stdint.h>

#include "app.h"
#include "drivers.h"

#define REG(addr) (*(volatile uint32_t *)(addr))
/* RCC */
#define RCC_BASE 0x40021000u
#define RCC_AHB2ENR REG(RCC_BASE + 0x4C)
#define RCC_APB1ENR1 REG(RCC_BASE + 0x58)
#define RCC_APB2ENR REG(RCC_BASE + 0x60)
/* GPIO */
#define GPIOB_BASE 0x48000400u
#define GPIOB_MODER REG(GPIOB_BASE + 0x00)
#define GPIOB_PUPDR REG(GPIOB_BASE + 0x0C)
#define GPIOB_BSRR REG(GPIOB_BASE + 0x18)
#define GPIOB_AFRL REG(GPIOB_BASE + 0x20)
#define GPIOC_BASE 0x48000800u
#define GPIOC_MODER REG(GPIOC_BASE + 0x00)
#define GPIOC_BSRR REG(GPIOC_BASE + 0x18)
/* TIM3 */
#define TIM3_BASE 0x40000400u
#define TIM3_CR1 REG(TIM3_BASE + 0x00)
#define TIM3_EGR REG(TIM3_BASE + 0x14)
#define TIM3_CCMR2 REG(TIM3_BASE + 0x1C)
#define TIM3_CCER REG(TIM3_BASE + 0x20)
#define TIM3_PSC REG(TIM3_BASE + 0x28)
#define TIM3_ARR REG(TIM3_BASE + 0x2C)
#define TIM3_CCR3 REG(TIM3_BASE + 0x3C)
#define TIM3_CCR4 REG(TIM3_BASE + 0x40)
/* SYSCFG / EXTI / NVIC */
#define SYSCFG_EXTICR2 REG(0x40010000u + 0x0C)
#define EXTI_IMR1 REG(0x40010400u + 0x00)
#define EXTI_FTSR1 REG(0x40010400u + 0x0C)
#define EXTI_PR1 REG(0x40010400u + 0x14)
#define NVIC_ISER0 REG(0xE000E100u)
#define EXTI4_IRQn 10
/* SysTick, IWDG, FPU */
#define SYST_CSR REG(0xE000E010u)
#define SYST_RVR REG(0xE000E014u)
#define SYST_CVR REG(0xE000E018u)
#define IWDG_KR REG(0x40003000u)
#define IWDG_PR REG(0x40003004u)
#define IWDG_RLR REG(0x40003008u)
#define SCB_CPACR REG(0xE000ED88u)

#define CORE_HZ 16000000u
#define PWM_ARR 999u /* 16 MHz / 16 / 1000 = 1 kHz */

static app_t g_app;
static volatile uint32_t g_ticks;

static hal_status_t i2c_stub(void *c, uint8_t a, const uint8_t *tx, size_t ntx, uint8_t *rx, size_t nrx)
{
    (void)c; (void)a; (void)tx; (void)ntx; (void)rx; (void)nrx;
    return HAL_TIMEOUT; /* I2C1 peripheral driver: board bring-up */
}

static void outputs_apply(const app_outputs_t *o)
{
    GPIOB_BSRR = o->radio_en ? (1u << 13) : (1u << (13 + 16));
    GPIOB_BSRR = o->payload_en ? (1u << 14) : (1u << (14 + 16));
    TIM3_CCR3 = (uint32_t)(o->duty_batt * (float)(PWM_ARR + 1));
    TIM3_CCR4 = (uint32_t)(o->duty_bay * (float)(PWM_ARR + 1));
}

void EXTI4_IRQHandler(void)
{
    EXTI_PR1 = 1u << 4; /* clear pending */
    app_power_fail_isr(&g_app);
    /* shed in hardware before returning: load switches off, heater PWM to 0 */
    GPIOB_BSRR = (1u << (13 + 16)) | (1u << (14 + 16));
    TIM3_CCR3 = 0;
    TIM3_CCR4 = 0;
}

void SysTick_Handler(void) { g_ticks++; }

static void board_init(void)
{
    SCB_CPACR |= 0xFu << 20; /* enable the FPU (CP10, CP11) */
    RCC_AHB2ENR |= (1u << 1) | (1u << 2); /* GPIOB, GPIOC */
    RCC_APB1ENR1 |= 1u << 1;              /* TIM3 */
    RCC_APB2ENR |= 1u << 0;               /* SYSCFG */

    /* PB13, PB14 outputs (load-switch ON, external pull-downs keep them off in reset) */
    GPIOB_BSRR = (1u << (13 + 16)) | (1u << (14 + 16));
    GPIOB_MODER = (GPIOB_MODER & ~((3u << 26) | (3u << 28))) | (1u << 26) | (1u << 28);
    /* PB0, PB1 alternate function 2 = TIM3_CH3, TIM3_CH4 */
    GPIOB_MODER = (GPIOB_MODER & ~(0xFu)) | (2u << 0) | (2u << 2);
    GPIOB_AFRL = (GPIOB_AFRL & ~0xFFu) | (2u << 0) | (2u << 4);
    /* PB4 input with pull-up (open-drain ALERT, external 10k too) */
    GPIOB_MODER &= ~(3u << 8);
    GPIOB_PUPDR = (GPIOB_PUPDR & ~(3u << 8)) | (1u << 8);
    /* PC13, PC14 LEDs (active low) */
    GPIOC_MODER = (GPIOC_MODER & ~((3u << 26) | (3u << 28))) | (1u << 26) | (1u << 28);

    /* TIM3: 1 kHz PWM mode 1 on CH3, CH4, preload enabled */
    TIM3_PSC = 15;
    TIM3_ARR = PWM_ARR;
    TIM3_CCMR2 = (6u << 4) | (1u << 3) | (6u << 12) | (1u << 11);
    TIM3_CCR3 = 0;
    TIM3_CCR4 = 0;
    TIM3_CCER = (1u << 8) | (1u << 12);
    TIM3_EGR = 1;
    TIM3_CR1 = (1u << 7) | 1u;

    /* PB4 falling edge -> EXTI4 */
    SYSCFG_EXTICR2 = (SYSCFG_EXTICR2 & ~0xFu) | 1u; /* port B */
    EXTI_FTSR1 |= 1u << 4;
    EXTI_IMR1 |= 1u << 4;
    NVIC_ISER0 = 1u << EXTI4_IRQn;

    /* SysTick 1 ms */
    SYST_RVR = CORE_HZ / 1000u - 1u;
    SYST_CVR = 0;
    SYST_CSR = 7u;

    /* IWDG: LSI 32 kHz / 32 = 1 kHz, 100 ms timeout */
    IWDG_KR = 0xCCCC;
    IWDG_KR = 0x5555;
    IWDG_PR = 3;
    IWDG_RLR = 100;
    IWDG_KR = 0xAAAA;
}

int main(void)
{
    board_init();
    app_init(&g_app);
    hal_i2c_t i2c1 = {i2c_stub, 0};
    app_inputs_t in = {0};
    uint32_t last = 0;
    for (;;) {
        while (g_ticks == last) {
        }
        last++;
        in.v_in = 14.8f; /* ADC2 IN12 (VIN_SENSE): board bring-up */
        in.new_slow_sample = (last % 1000u) == 0;
        if (in.new_slow_sample) {
            in.t_bay_ok = tmp117_read_c(i2c1, 0x48, &in.t_bay_c) == HAL_OK;
            in.t_batt_ok = false;
        }
        outputs_apply(app_tick_1ms(&g_app, &in));
        GPIOC_BSRR = (g_app.h_batt.faults | g_app.h_bay.faults) ? (1u << (14 + 16)) : (1u << 14);
        IWDG_KR = 0xAAAA;
    }
}
